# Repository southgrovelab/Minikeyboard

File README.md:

# Minikeyboard
A small, USB-drive-sized keyboard with four keys: Esc, Tab, Enter, and Ctrl-Alt-Delete. There is room for three additional keys.  

Rev_A is a like a HAT for a Raspberry Pi Pico  

## Note!
*The software for Rev A is designed for four buttons only.*  
*GPIO2, GPIO4, GPIO6, and GPIO8!*

Rev_B is going to be more like a USB-drive-sized keyboard

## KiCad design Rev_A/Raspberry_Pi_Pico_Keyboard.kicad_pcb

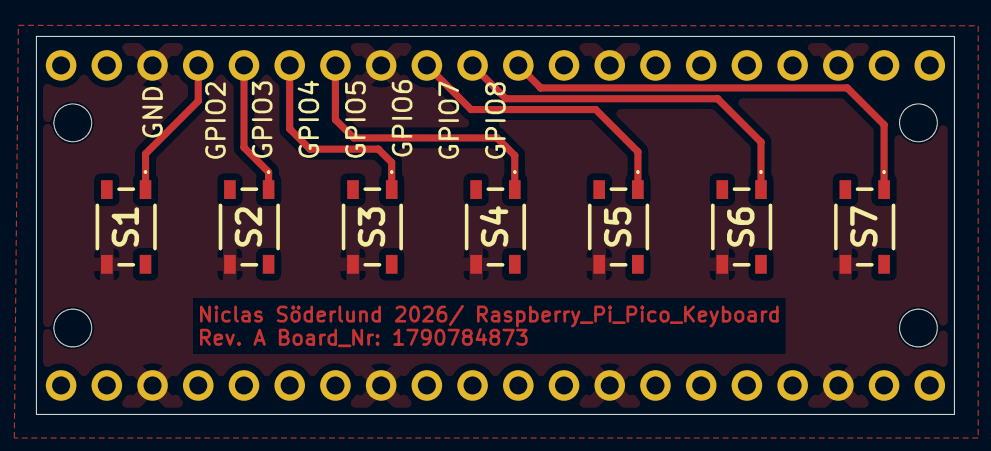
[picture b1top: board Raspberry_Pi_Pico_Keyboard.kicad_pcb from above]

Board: 2 copper layers, 51.0 x 21.0 mm, 9 parts (0 on the bottom side), 8 nets.

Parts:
J1, J2: Conn_01x20_Pin; PinHeader_1x20_P2.54mm_Vertical
S1, S2, S3, S4, S5, S6, S7: SKRPABE010

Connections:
/GPIO2: J2.37, S1.1
/GPIO3: J2.36, S2.1
/GPIO4: J2.35, S3.1
/GPIO5: J2.34, S4.1
/GPIO6: J2.32, S5.1
/GPIO7: J2.31, S6.1
/GPIO8: J2.30, S7.1
GND: J1.3, J1.8, J1.13, J1.18, J2.23, J2.28, J2.33, J2.38, S1.4, S2.4, S3.4, S4.4, S5.4, S6.4, S7.4

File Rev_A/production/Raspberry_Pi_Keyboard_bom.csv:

Designator,Footprint,Quantity,Value,LCSC Part #
"J1, J2",PinHeader_1x20_P2.54mm_Vertical,2,Conn_01x20_Pin,
"S1, S2, S3, S4, S5, S6, S7",SKRPABE010,7,SKHUALE010 Tactile,
